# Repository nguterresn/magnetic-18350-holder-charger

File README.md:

<!-- Improved compatibility of back to top link: See: https://github.com/othneildrew/Best-README-Template/pull/73 -->

<!-- PROJECT LOGO -->
<br />
<div align="center">
<h3 align="center">Magnetic 18350 battery holder and charger</h3>

  <p align="center">
    Lithium Battery 18350 3.7V One Cell Holder and Charger. Battery charging is held by the <a href="https://dlnmh9ip6v2uc.cloudfront.net/datasheets/Prototyping/TP4056.pdf">TP4056 </a> IC.
    <br>
    <a href="https://github.com/nguterresn/magnetic-18350-holder-charger
/issues">Report Bug</a>
    ·
    <a href="https://github.com/nguterresn/magnetic-18350-holder-charger/issues">Request Feature</a>
  </p>
</div>

<!-- TABLE OF CONTENTS -->
<!-- <details>
  <summary>Table of Contents</summary>
  <ol>
    <li>
      <a href="#about-the-project">About The Project</a>
      <ul>
        <li><a href="#built-with">Built With</a></li>
      </ul>
    </li>
<!--     <li><a href="#usage">Usage</a></li> -->
<!--     <li><a href="#roadmap">Roadmap</a></li> -->
<!--     <li><a href="#contributing">Contributing</a></li> -->
<!--     <li><a href="#license">License</a></li> -->
<!--     <li><a href="#contact">Contact</a></li> -->
<!--     <li><a href="#acknowledgments">Acknowledgments</a></li> -->
<!--   </ol> -->
<!-- </details> -->

<!-- ABOUT THE PROJECT -->
## About The Project

This project aims to build an easy to use battery holder. The battery is a one cell 3.7V 18350 type and it is charged by the IC TP4056. The battery can be charger through USB-C and it is rated at 500mA. 
The magnetic connector is a circular 10mm diameter circle which receives either positive voltage at the center or the ground around the circle circumference.

<p align="right">(<a href="#readme-top">back to top</a>)</p>

## Symbols and Footprints designed

### Symbols

All the symbols are in the same symbol library [here](https://github.com/nguterresn/magnetic-18350-holder-charger/blob/master/pcb/magnetic-18350-holder-charger/New_Library.kicad_sym).

### Footprints

- [TP4056](https://github.com/nguterresn/magnetic-18350-holder-charger/blob/master/pcb/magnetic-18350-holder-charger/NewLibraryFootprint.pretty/BatteryCharger4096.kicad_mod)
- [Lithium 18350 1P Holder](https://github.com/nguterresn/magnetic-18350-holder-charger/blob/master/pcb/magnetic-18350-holder-charger/NewLibraryFootprint.pretty/18350-Holder.kicad_mod)
- [Magnetic Connector](https://github.com/nguterresn/magnetic-18350-holder-charger/blob/master/pcb/magnetic-18350-holder-charger/NewLibraryFootprint.pretty/MagneticInput.kicad_mod)

<!-- GETTING STARTED -->
<!-- ## Getting Started

This is an example of how you may give instructions on setting up your project locally.
To get a local copy up and running follow these simple example steps.

### Prerequisites

This is an example of how to list things you need to use the software and how to install them.
* npm
  ```sh
  npm install npm@latest -g
  ```

### Installation

1. Get a free API Key at [https://example.com](https://example.com)
2. Clone the repo
   ```sh
   git clone https://github.com/github_username/repo_name.git
   ```
3. Install NPM packages
   ```sh
   npm install
   ```
4. Enter your API in `config.js`
   ```js
   const API_KEY = 'ENTER YOUR API';
   ```

<p align="right">(<a href="#readme-top">back to top</a>)</p>
 -->

<!-- USAGE EXAMPLES -->
<!-- ## Usage

Use this space to show useful examples of how a project can be used. Additional screenshots, code examples and demos work well in this space. You may also link to more resources.

_For more examples, please refer to the [Documentation](https://example.com)_

<p align="right">(<a href="#readme-top">back to top</a>)</p> -->

<!-- 
## Roadmap

- [ ] Feature 1
- [ ] Feature 2
- [ ] Feature 3
    - [ ] Nested Feature

See the [open issues](https://github.com/github_username/repo_name/issues) for a full list of proposed features (and known issues).

<p align="right">(<a href="#readme-top">back to top</a>)</p> -->

<!-- CONTRIBUTING -->
<!-- ## Contributing

Contributions are what make the open source community such an amazing place to learn, inspire, and create. Any contributions you make are **greatly appreciated**.

If you have a suggestion that would make this better, please fork the repo and create a pull request. You can also simply open an issue with the tag "enhancement".
Don't forget to give the project a star! Thanks again!

1. Fork the Project
2. Create your Feature Branch (`git checkout -b feature/AmazingFeature`)
3. Commit your Changes (`git commit -m 'Add some AmazingFeature'`)
4. Push to the Branch (`git push origin feature/AmazingFeature`)
5. Open a Pull Request

<p align="right">(<a href="#readme-top">back to top</a>)</p> -->

<!-- LICENSE -->
<!-- ## License

Distributed under the MIT License. See `LICENSE.txt` for more information.

<p align="right">(<a href="#readme-top">back to top</a>)</p> -->

<!-- CONTACT -->
## Contact

Nuno Nogueira - [@nunoguterres](https://twitter.com/nunoguterres) - guterresnogueira@gmail.com

<p align="right">(<a href="#readme-top">back to top</a>)</p>

<!-- ACKNOWLEDGMENTS -->
<!-- ## Acknowledgments

* 
* 
* 

<p align="right">(<a href="#readme-top">back to top</a>)</p> -->

<!-- MARKDOWN LINKS & IMAGES -->
<!-- https://www.markdownguide.org/basic-syntax/#reference-style-links -->

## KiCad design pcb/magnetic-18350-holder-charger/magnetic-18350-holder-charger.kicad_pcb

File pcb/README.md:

## Description
##### This is where the pcb files are. Normally, here is where a KiCad project is created.

## Directory Structure

- **pcb**
    - bom
    - gerber
    - svg
    - ... (some package folders)

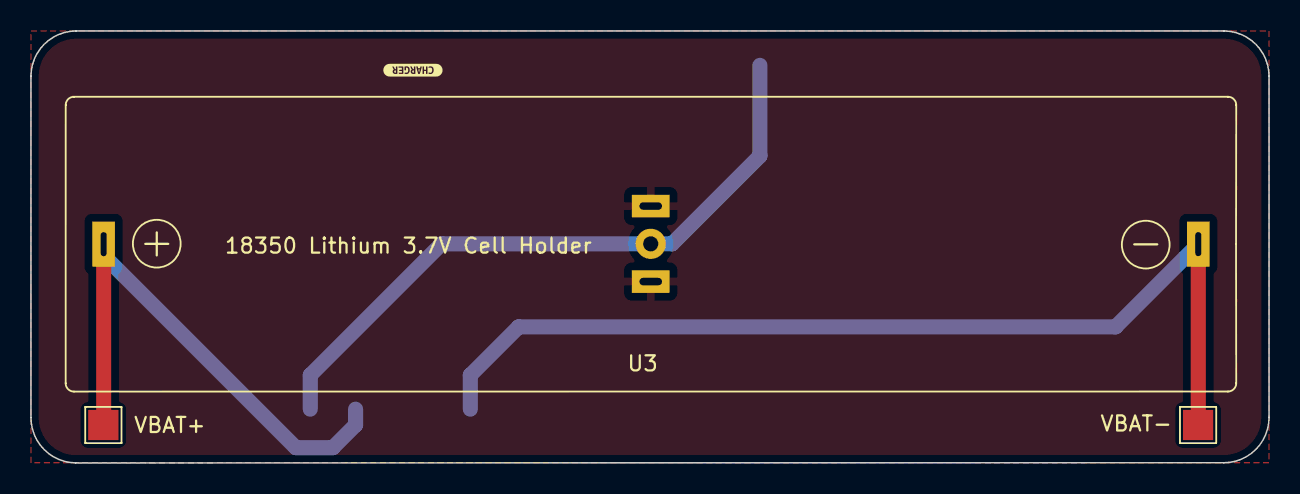
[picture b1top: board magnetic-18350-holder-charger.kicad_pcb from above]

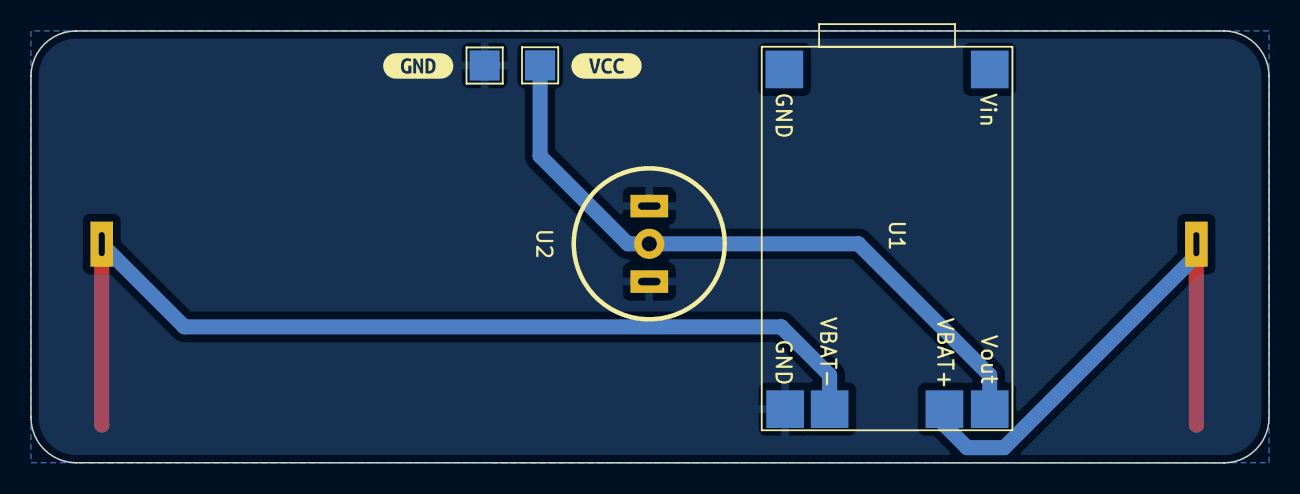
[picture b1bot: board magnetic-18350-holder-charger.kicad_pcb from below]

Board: 2 copper layers, 82.0 x 28.6 mm, 8 parts (4 on the bottom side), 4 nets.

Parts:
U1: BatteryCharger4096
U2: MagneticInput
U3: 18350-HOLDER; 18350-Holder
VBAT+: TestPoint_Pad_2.0x2.0mm
VBAT-: TestPoint_Pad_2.0x2.0mm
kibuzzard-63271A4C: G***; kibuzzard-63271A4C
kibuzzard-63272079: G***; kibuzzard-63272079
kibuzzard-63272085: G***; kibuzzard-63272085

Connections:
GND: U1.4 (Vout-), U2.2 (GND), U2.3 (GND)
unnamed: U1.3 (Vout+), U2.1 (V+)
unnamed: U1.5 (Bat+), U3.1 (V+), VBAT+.1
unnamed: U1.6 (Bat-), U3.2 (V-), VBAT-.1

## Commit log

2022-09-18 First commit.
2022-09-18 PCB Done!
2022-09-18 Added a pad to test vcc.
2022-09-18 Added 3d models
2022-10-16 Added case
